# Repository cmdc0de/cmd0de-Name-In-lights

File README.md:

# cmd0de-Name-In-lights
ATTiny13 + 60 APA104s + my New voltera one
* ensure you use the DRC file that voltera provides and is checked into this repo

ATTiny13a + 60 APA104s + Bantam Tool PCB Mill
* I just used my voltera DRC but the mill can go with smaller closer traces
* Remember to increase the isolation otherwise solider will bridge given a space of only 10 mils between traces
* I used my Voltera to solider and reflow the board after the bantam mill, milled the board

Arduino base code thanks to:  https://wp.josh.com/2014/05/13/ws2812-neopixels-are-not-so-finicky-once-you-get-to-know-them/
and his source here:  https://github.com/bigjosh/SimpleNeoPixelDemo

To program ATTiny13a I used the public doc from instructables check into this repo.

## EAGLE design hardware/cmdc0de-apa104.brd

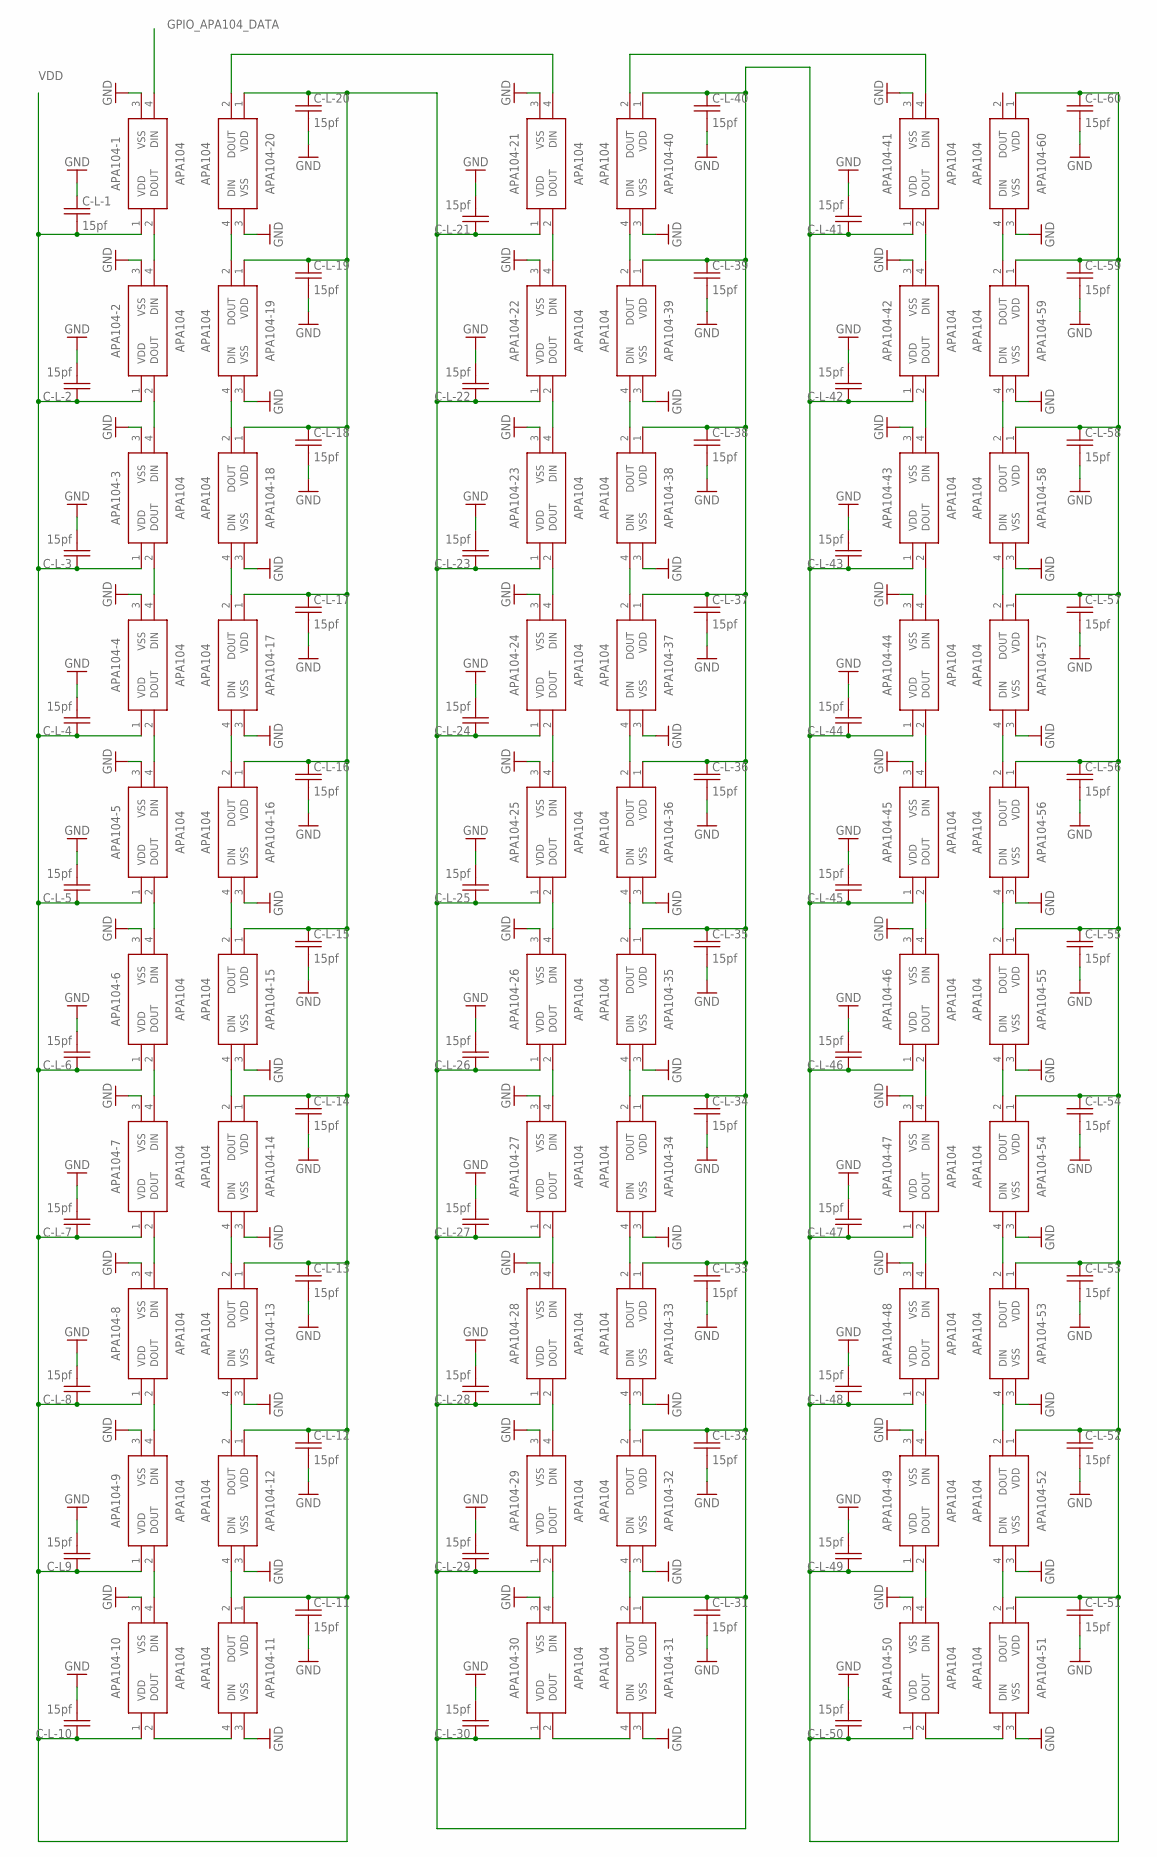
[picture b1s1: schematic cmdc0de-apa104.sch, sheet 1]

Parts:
APA104-1, APA104-2, APA104-3, APA104-4, APA104-5, APA104-6, APA104-7, APA104-8, APA104-9, APA104-10, APA104-11, APA104-12, APA104-13, APA104-14, APA104-15, APA104-16, APA104-17, APA104-18, APA104-19, APA104-20, APA104-21, APA104-22, APA104-23, APA104-24, APA104-25, APA104-26, APA104-27, APA104-28, APA104-29, APA104-30, APA104-31, APA104-32, APA104-33, APA104-34, APA104-35, APA104-36, APA104-37, APA104-38, APA104-39, APA104-40, APA104-41, APA104-42, APA104-43, APA104-44, APA104-45, APA104-46, APA104-47, APA104-48, APA104-49, APA104-50, APA104-51, APA104-52, APA104-53, APA104-54, APA104-55, APA104-56, APA104-57, APA104-58, APA104-59, APA104-60: APA104
C-L9: 15pf; C0805-VOLTA
C-L-1, C-L-2, C-L-3, C-L-4, C-L-5, C-L-6, C-L-7, C-L-8, C-L-10, C-L-11, C-L-12, C-L-13, C-L-14, C-L-15, C-L-16, C-L-17, C-L-18, C-L-19, C-L-20, C-L-21, C-L-22, C-L-23, C-L-24, C-L-25, C-L-26, C-L-27, C-L-28, C-L-29, C-L-30, C-L-31, C-L-32, C-L-33, C-L-34, C-L-35, C-L-36, C-L-37, C-L-38, C-L-39, C-L-40, C-L-41, C-L-42, C-L-43, C-L-44, C-L-45, C-L-46, C-L-47, C-L-48, C-L-49, C-L-50, C-L-51, C-L-52, C-L-53, C-L-54, C-L-55, C-L-56, C-L-57, C-L-58, C-L-59, C-L-60: 15pf; C0805-VOLTA

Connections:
GND: APA104-1.3 (VSS), APA104-2.3 (VSS), APA104-3.3 (VSS), APA104-4.3 (VSS), APA104-5.3 (VSS), APA104-6.3 (VSS), APA104-7.3 (VSS), APA104-8.3 (VSS), APA104-9.3 (VSS), APA104-10.3 (VSS), APA104-11.3 (VSS), APA104-12.3 (VSS), APA104-13.3 (VSS), APA104-14.3 (VSS), APA104-15.3 (VSS), APA104-16.3 (VSS), APA104-17.3 (VSS), APA104-18.3 (VSS), APA104-19.3 (VSS), APA104-20.3 (VSS), APA104-21.3 (VSS), APA104-22.3 (VSS), APA104-23.3 (VSS), APA104-24.3 (VSS), APA104-25.3 (VSS), APA104-26.3 (VSS), APA104-27.3 (VSS), APA104-28.3 (VSS), APA104-29.3 (VSS), APA104-30.3 (VSS), APA104-31.3 (VSS), APA104-32.3 (VSS), APA104-33.3 (VSS), APA104-34.3 (VSS), APA104-35.3 (VSS), APA104-36.3 (VSS), APA104-37.3 (VSS), APA104-38.3 (VSS), APA104-39.3 (VSS), APA104-40.3 (VSS), APA104-41.3 (VSS), APA104-42.3 (VSS), APA104-43.3 (VSS), APA104-44.3 (VSS), APA104-45.3 (VSS), APA104-46.3 (VSS), APA104-47.3 (VSS), APA104-48.3 (VSS), APA104-49.3 (VSS), APA104-50.3 (VSS), APA104-51.3 (VSS), APA104-52.3 (VSS), APA104-53.3 (VSS), APA104-54.3 (VSS), APA104-55.3 (VSS), APA104-56.3 (VSS), APA104-57.3 (VSS), APA104-58.3 (VSS), APA104-59.3 (VSS), APA104-60.3 (VSS), C-L9.2, C-L-1.1, C-L-2.2, C-L-3.2, C-L-4.2, C-L-5.2, C-L-6.2, C-L-7.2, C-L-8.2, C-L-10.2, C-L-11.2, C-L-12.2, C-L-13.2, C-L-14.2, C-L-15.2, C-L-16.2, C-L-17.2, C-L-18.2, C-L-19.2, C-L-20.2, C-L-21.2, C-L-22.2, C-L-23.2, C-L-24.2, C-L-25.2, C-L-26.2, C-L-27.2, C-L-28.2, C-L-29.2, C-L-30.2, C-L-31.2, C-L-32.2, C-L-33.2, C-L-34.2, C-L-35.2, C-L-36.2, C-L-37.2, C-L-38.2, C-L-39.2, C-L-40.2, C-L-41.2, C-L-42.2, C-L-43.2, C-L-44.2, C-L-45.2, C-L-46.2, C-L-47.2, C-L-48.2, C-L-49.2, C-L-50.2, C-L-51.2, C-L-52.2, C-L-53.2, C-L-54.2, C-L-55.2, C-L-56.2, C-L-57.2, C-L-58.2, C-L-59.2, C-L-60.2; also elsewhere on the board
GPIO_APA104_DATA: APA104-1.4 (DIN); also elsewhere on the board
GPIO_APA104_DATA1: APA104-40.2 (DOUT), APA104-41.4 (DIN)
unnamed: APA104-2.2 (DOUT), APA104-3.4 (DIN)
unnamed: APA104-3.2 (DOUT), APA104-4.4 (DIN)
unnamed: APA104-4.2 (DOUT), APA104-5.4 (DIN)
unnamed: APA104-5.2 (DOUT), APA104-6.4 (DIN)
unnamed: APA104-6.2 (DOUT), APA104-7.4 (DIN)
unnamed: APA104-7.2 (DOUT), APA104-8.4 (DIN)
unnamed: APA104-8.2 (DOUT), APA104-9.4 (DIN)
unnamed: APA104-9.2 (DOUT), APA104-10.4 (DIN)
unnamed: APA104-10.2 (DOUT), APA104-11.4 (DIN)
unnamed: APA104-11.2 (DOUT), APA104-12.4 (DIN)
unnamed: APA104-12.2 (DOUT), APA104-13.4 (DIN)
unnamed: APA104-13.2 (DOUT), APA104-14.4 (DIN)
unnamed: APA104-14.2 (DOUT), APA104-15.4 (DIN)
unnamed: APA104-15.2 (DOUT), APA104-16.4 (DIN)
unnamed: APA104-16.2 (DOUT), APA104-17.4 (DIN)
unnamed: APA104-17.2 (DOUT), APA104-18.4 (DIN)
unnamed: APA104-18.2 (DOUT), APA104-19.4 (DIN)
unnamed: APA104-19.2 (DOUT), APA104-20.4 (DIN)
unnamed: APA104-21.2 (DOUT), APA104-22.4 (DIN)
unnamed: APA104-22.2 (DOUT), APA104-23.4 (DIN)
unnamed: APA104-23.2 (DOUT), APA104-24.4 (DIN)
unnamed: APA104-24.2 (DOUT), APA104-25.4 (DIN)
unnamed: APA104-25.2 (DOUT), APA104-26.4 (DIN)
unnamed: APA104-26.2 (DOUT), APA104-27.4 (DIN)
unnamed: APA104-27.2 (DOUT), APA104-28.4 (DIN)
unnamed: APA104-28.2 (DOUT), APA104-29.4 (DIN)
unnamed: APA104-29.2 (DOUT), APA104-30.4 (DIN)
unnamed: APA104-30.2 (DOUT), APA104-31.4 (DIN)
unnamed: APA104-20.2 (DOUT), APA104-21.4 (DIN)
unnamed: APA104-41.2 (DOUT), APA104-42.4 (DIN)
unnamed: APA104-1.2 (DOUT), APA104-2.4 (DIN)
unnamed: APA104-31.2 (DOUT), APA104-32.4 (DIN)
unnamed: APA104-32.2 (DOUT), APA104-33.4 (DIN)
unnamed: APA104-33.2 (DOUT), APA104-34.4 (DIN)
unnamed: APA104-34.2 (DOUT), APA104-35.4 (DIN)
unnamed: APA104-35.2 (DOUT), APA104-36.4 (DIN)
unnamed: APA104-36.2 (DOUT), APA104-37.4 (DIN)
unnamed: APA104-37.2 (DOUT), APA104-38.4 (DIN)
unnamed: APA104-38.2 (DOUT), APA104-39.4 (DIN)
unnamed: APA104-39.2 (DOUT), APA104-40.4 (DIN)
unnamed: APA104-50.2 (DOUT), APA104-51.4 (DIN)
unnamed: APA104-42.2 (DOUT), APA104-43.4 (DIN)
unnamed: APA104-43.2 (DOUT), APA104-44.4 (DIN)
unnamed: APA104-44.2 (DOUT), APA104-45.4 (DIN)
unnamed: APA104-45.2 (DOUT), APA104-46.4 (DIN)
unnamed: APA104-46.2 (DOUT), APA104-47.4 (DIN)
unnamed: APA104-47.2 (DOUT), APA104-48.4 (DIN)
unnamed: APA104-48.2 (DOUT), APA104-49.4 (DIN)
unnamed: APA104-49.2 (DOUT), APA104-50.4 (DIN)
unnamed: APA104-51.2 (DOUT), APA104-52.4 (DIN)
unnamed: APA104-52.2 (DOUT), APA104-53.4 (DIN)
unnamed: APA104-53.2 (DOUT), APA104-54.4 (DIN)
unnamed: APA104-54.2 (DOUT), APA104-55.4 (DIN)
unnamed: APA104-55.2 (DOUT), APA104-56.4 (DIN)
unnamed: APA104-56.2 (DOUT), APA104-57.4 (DIN)
unnamed: APA104-57.2 (DOUT), APA104-58.4 (DIN)
unnamed: APA104-58.2 (DOUT), APA104-59.4 (DIN)
unnamed: APA104-59.2 (DOUT), APA104-60.4 (DIN)
VDD: APA104-1.1 (VDD), APA104-2.1 (VDD), APA104-3.1 (VDD), APA104-4.1 (VDD), APA104-5.1 (VDD), APA104-6.1 (VDD), APA104-7.1 (VDD), APA104-8.1 (VDD), APA104-9.1 (VDD), APA104-10.1 (VDD), APA104-11.1 (VDD), APA104-12.1 (VDD), APA104-13.1 (VDD), APA104-14.1 (VDD), APA104-15.1 (VDD), APA104-16.1 (VDD), APA104-17.1 (VDD), APA104-18.1 (VDD), APA104-19.1 (VDD), APA104-20.1 (VDD), APA104-21.1 (VDD), APA104-22.1 (VDD), APA104-23.1 (VDD), APA104-24.1 (VDD), APA104-25.1 (VDD), APA104-26.1 (VDD), APA104-27.1 (VDD), APA104-28.1 (VDD), APA104-29.1 (VDD), APA104-30.1 (VDD), APA104-31.1 (VDD), APA104-32.1 (VDD), APA104-33.1 (VDD), APA104-34.1 (VDD), APA104-35.1 (VDD), APA104-36.1 (VDD), APA104-37.1 (VDD), APA104-38.1 (VDD), APA104-39.1 (VDD), APA104-40.1 (VDD), APA104-41.1 (VDD), APA104-42.1 (VDD), APA104-43.1 (VDD), APA104-44.1 (VDD), APA104-45.1 (VDD), APA104-46.1 (VDD), APA104-47.1 (VDD), APA104-48.1 (VDD), APA104-49.1 (VDD), APA104-50.1 (VDD), APA104-51.1 (VDD), APA104-52.1 (VDD), APA104-53.1 (VDD), APA104-54.1 (VDD), APA104-55.1 (VDD), APA104-56.1 (VDD), APA104-57.1 (VDD), APA104-58.1 (VDD), APA104-59.1 (VDD), APA104-60.1 (VDD), C-L9.1, C-L-1.2, C-L-2.1, C-L-3.1, C-L-4.1, C-L-5.1, C-L-6.1, C-L-7.1, C-L-8.1, C-L-10.1, C-L-11.1, C-L-12.1, C-L-13.1, C-L-14.1, C-L-15.1, C-L-16.1, C-L-17.1, C-L-18.1, C-L-19.1, C-L-20.1, C-L-21.1, C-L-22.1, C-L-23.1, C-L-24.1, C-L-25.1, C-L-26.1, C-L-27.1, C-L-28.1, C-L-29.1, C-L-30.1, C-L-31.1, C-L-32.1, C-L-33.1, C-L-34.1, C-L-35.1, C-L-36.1, C-L-37.1, C-L-38.1, C-L-39.1, C-L-40.1, C-L-41.1, C-L-42.1, C-L-43.1, C-L-44.1, C-L-45.1, C-L-46.1, C-L-47.1, C-L-48.1, C-L-49.1, C-L-50.1, C-L-51.1, C-L-52.1, C-L-53.1, C-L-54.1, C-L-55.1, C-L-56.1, C-L-57.1, C-L-58.1, C-L-59.1, C-L-60.1; also elsewhere on the board

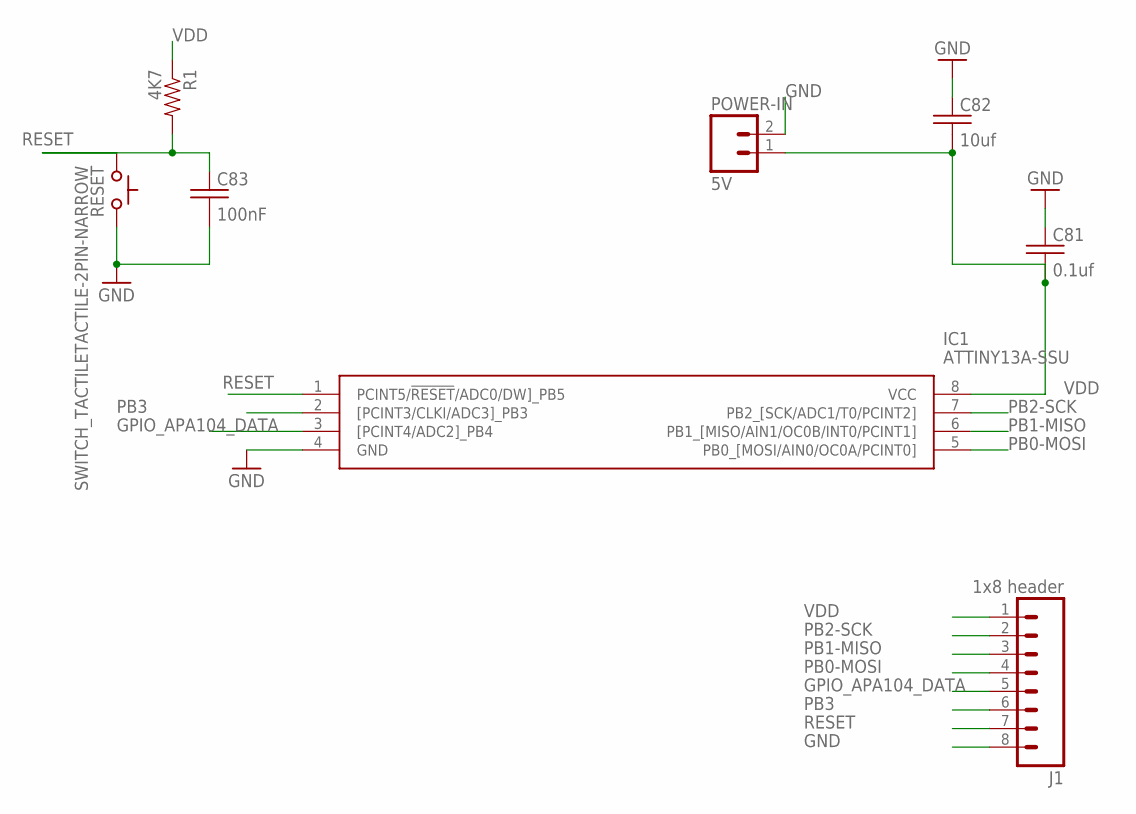
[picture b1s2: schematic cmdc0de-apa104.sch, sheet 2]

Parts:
C81: 0.1uf; C0805-VOLTA
C82: 10uf; C0805-VOLTA
C83: 100nF; C0805-VOLTA
IC1: ATTINY13A-SSU; SOIC127P600X175-8N
J1: 1x8 header; 1X08
POWER-IN: 5V; 1X02
R1: 4K7; 0805
RESET: SWITCH_TACTILETACTILE-2PIN-NARROW; TACTILE-2PIN-NARROW

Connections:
GND: C81.1, C82.1, C83.2, IC1.4 (GND), J1.8, POWER-IN.2, RESET.P$1 (A); also elsewhere on the board
GPIO_APA104_DATA: IC1.3 ([PCINT4/ADC2]_PB4), J1.5; also elsewhere on the board
PB0-MOSI: IC1.5 (PB0_[MOSI/AIN0/OC0A/PCINT0]), J1.4
PB1-MISO: IC1.6 (PB1_[MISO/AIN1/OC0B/INT0/PCINT1]), J1.3
PB2-SCK: IC1.7 (PB2_[SCK/ADC1/T0/PCINT2]), J1.2
PB3: IC1.2 ([PCINT3/CLKI/ADC3]_PB3), J1.6
RESET: C83.1, IC1.1 (PCINT5/!RESET!/ADC0/DW]_PB5), J1.7, R1.2, RESET.P$2 (C)
VDD: C81.2, C82.2, IC1.8 (VCC), J1.1, POWER-IN.1, R1.1; also elsewhere on the board

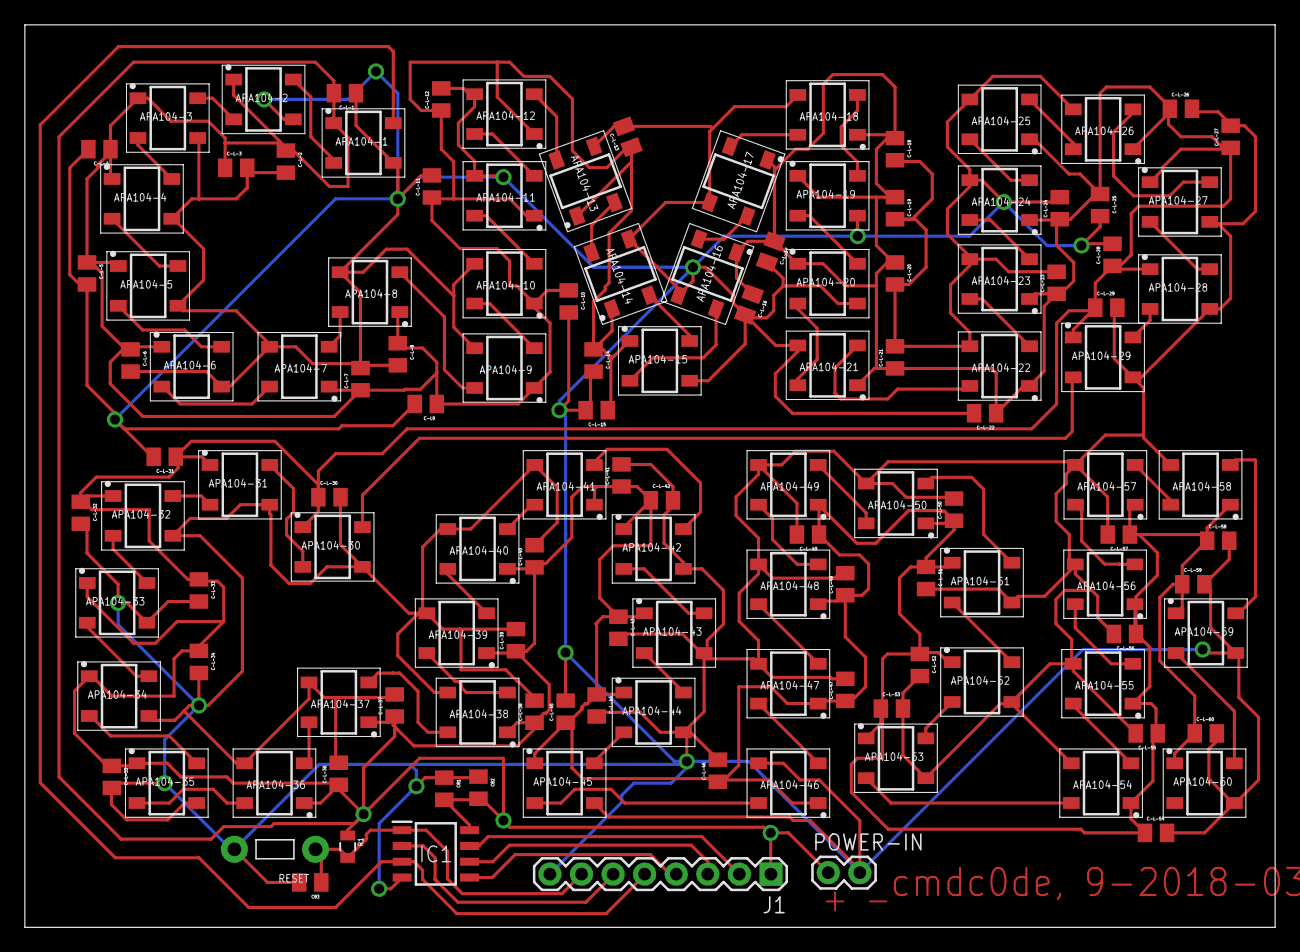
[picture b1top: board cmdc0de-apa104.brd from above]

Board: 2 copper layers, 100.6 x 72.6 mm, 128 parts (0 on the bottom side), 67 nets.

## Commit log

2018-09-02 board is in a initial layout config
2018-09-03 no errors board is complete?
2018-09-03 fixed wire pieces
2018-09-04 board and gerbers
2018-09-04 added .7 mm as min diameter, removed gnd plane and traced them instead due to how voltera works
2018-09-05 spaced a few traces farther apart and got the rev as a larger font
2018-09-08 more tweaking to get distances right
2018-09-10 moved wires farther apart again
2018-09-14 new dru file with real limits for voltera
2018-10-14 working board and software
